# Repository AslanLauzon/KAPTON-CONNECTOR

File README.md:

## Kapton Heater System for Oxidizer Tank Pressure Regulation

This system uses a 24V, 14.6A Kapton trace heater to regulate the pressure inside a nitrous oxide oxidizer tank, particularly in colder environments where vapor pressure drops below optimal levels. The heater is PWM-controlled via a high-current N-channel MOSFET, allowing for precise thermal regulation.

Designed by Brandon Moncriefe, Zhihan Cai and Aslan Lauzon for QRET

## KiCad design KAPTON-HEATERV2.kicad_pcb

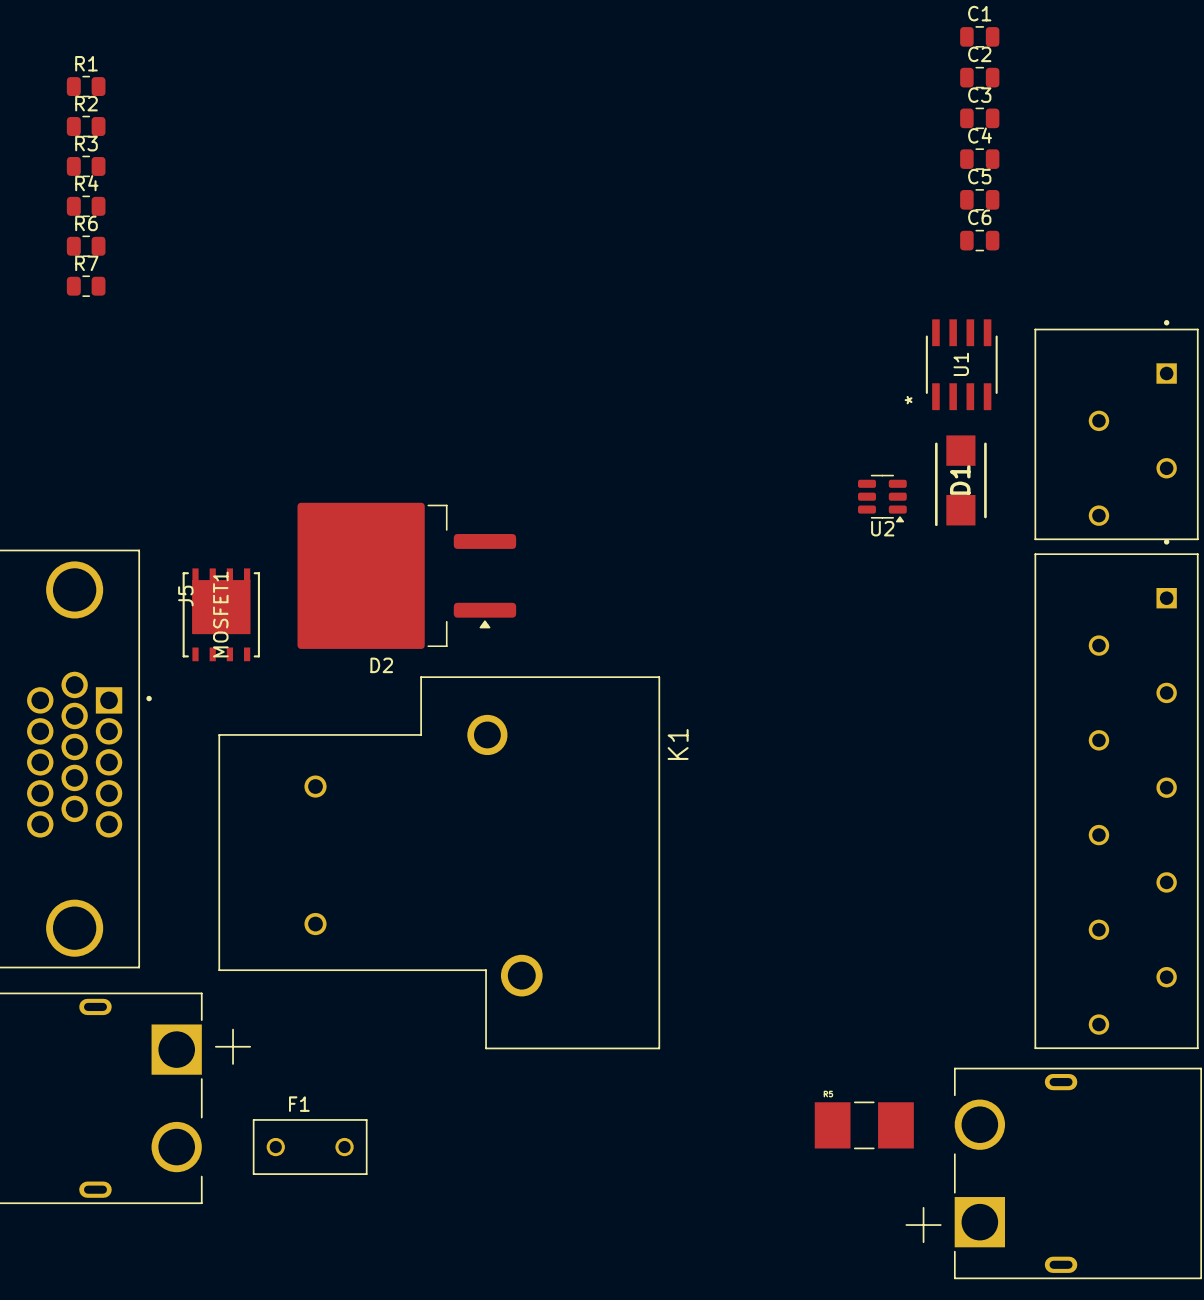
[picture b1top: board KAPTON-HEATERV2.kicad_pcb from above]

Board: 2 copper layers, 25 parts (0 on the bottom side), 25 nets, no tracks yet.

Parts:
C1, C3: C4.7uf; C_0805_2012Metric
C2, C5: C0.1uf; C_0805_2012Metric
C4: C19nf; C_0805_2012Metric
C6: C0.1u; C_0805_2012Metric
D1: MBRS1100T3G; DIOM5436X247N
D2: V20DM100C-M3/I; TO-263-2
F1: 14 Amp Fuse; FUSRR508W60L835T400H810
J1, J2: XT60PW-M; AMASS_XT60PW-M
J3: 1985276; PHOENIX_1985276
J4: 1985218; TE_1985218
J5: 10090926-P154XLF; AMPHENOL_10090926-P154XLF
K1: 1-1393210-8; RELAY_1-1393210-8
MOSFET1: SIR462DP-T1-GE3; POWERPAK_SO-8_SINGLE_VIS
R1, R2: 100; R_0805_2012Metric
R3: R100k; R_0805_2012Metric
R4: 4.7k; R_0805_2012Metric
R5: R0.001; RESC6432X90N
R6: R10; R_0805_2012Metric
R7: R1k; R_0805_2012Metric
U1: TC4427ACOA; SOIC8-N_MC_MCH
U2: INA181; SOT-23-6

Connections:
5V: C3.2, C5.2, D1.1 (K), J4.4, J5.11, K1.1, U2.6 (V+)
10V: C1.1, C2.1, J4.3, U1.6 (VDD)
10V PWM: R6.2, U1.7 (OUT_A)
/24V: D2.1 (K), J1.1, K1.4
/24VIN: F1.1, J2.2
Current Vout: C6.1, J3.10, R7.1
GND: C1.2, C2.2, C3.1, C4.2, C5.1, C6.2, J2.1, J5.10, J5.S1 (SHIELD), J5.S2 (SHIELD__1), MOSFET1.1, MOSFET1.2, MOSFET1.3, R3.2, R4.2, U1.3 (GND), U1.4 (INPUT_B), U2.2 (GND), U2.5 (REF)
HEATER OUT: D2.2 (A), MOSFET1.5, MOSFET1.6, MOSFET1.7, MOSFET1.8, R5.1, U2.4 (-)
unnamed: C4.1, MOSFET1.4, R6.1
unnamed: D1.2 (A), K1.2
unnamed: R1.2, R4.1
unnamed: R7.2, U2.1
unnamed: R2.2, R3.1, U1.2 (INPUT_A)
PWM: J4.1, R2.1
RELAY: J4.2, R1.1
SHUNT HIGH: J1.2, R5.2, U2.3 (+)
TH1: J3.1, J5.1
TH2: J3.2, J5.2
TH3: J3.3, J5.3
TH4: J3.4, J5.4
TH5: J3.5, J5.5
TH6: J3.6, J5.15
TH7: J3.7, J5.14
TH8: J3.8, J5.13
TH9: J3.9, J5.12

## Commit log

2025-06-18 started new one
2025-06-18 added tvs diode
2025-11-11 readme changes
